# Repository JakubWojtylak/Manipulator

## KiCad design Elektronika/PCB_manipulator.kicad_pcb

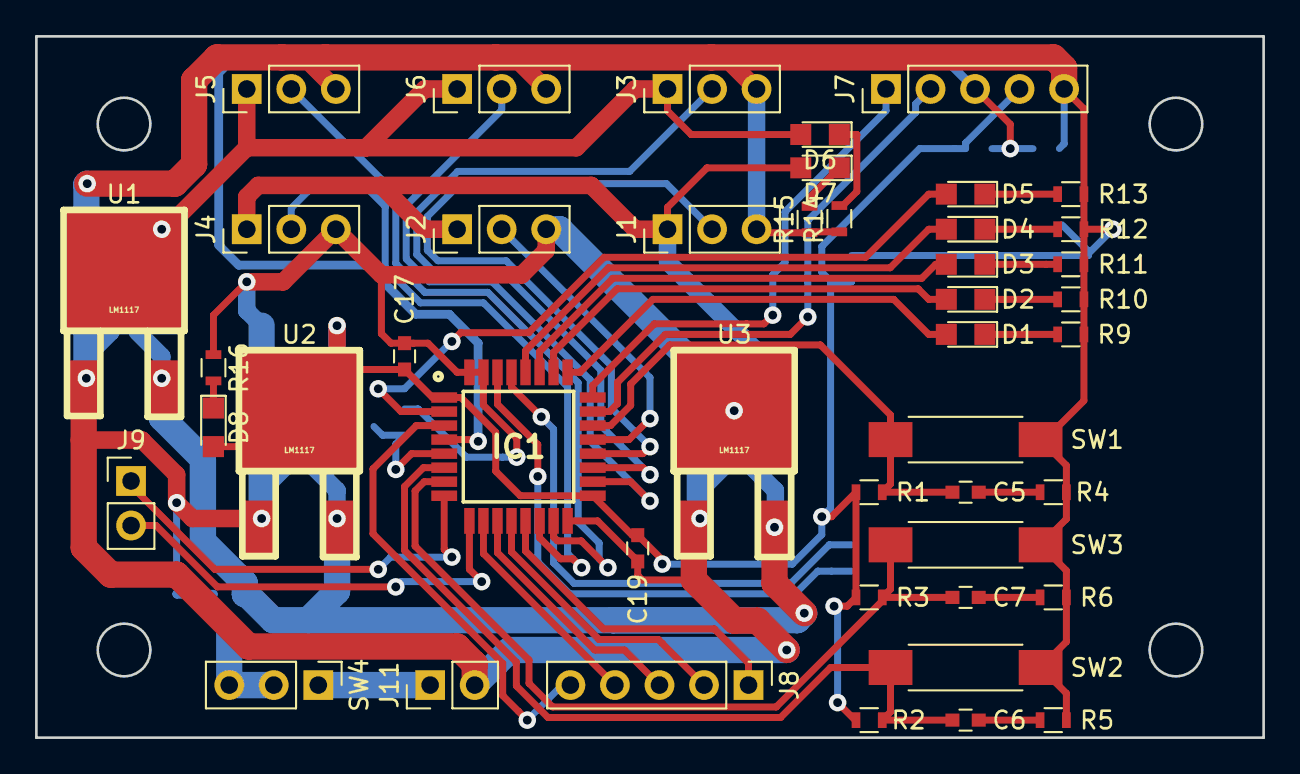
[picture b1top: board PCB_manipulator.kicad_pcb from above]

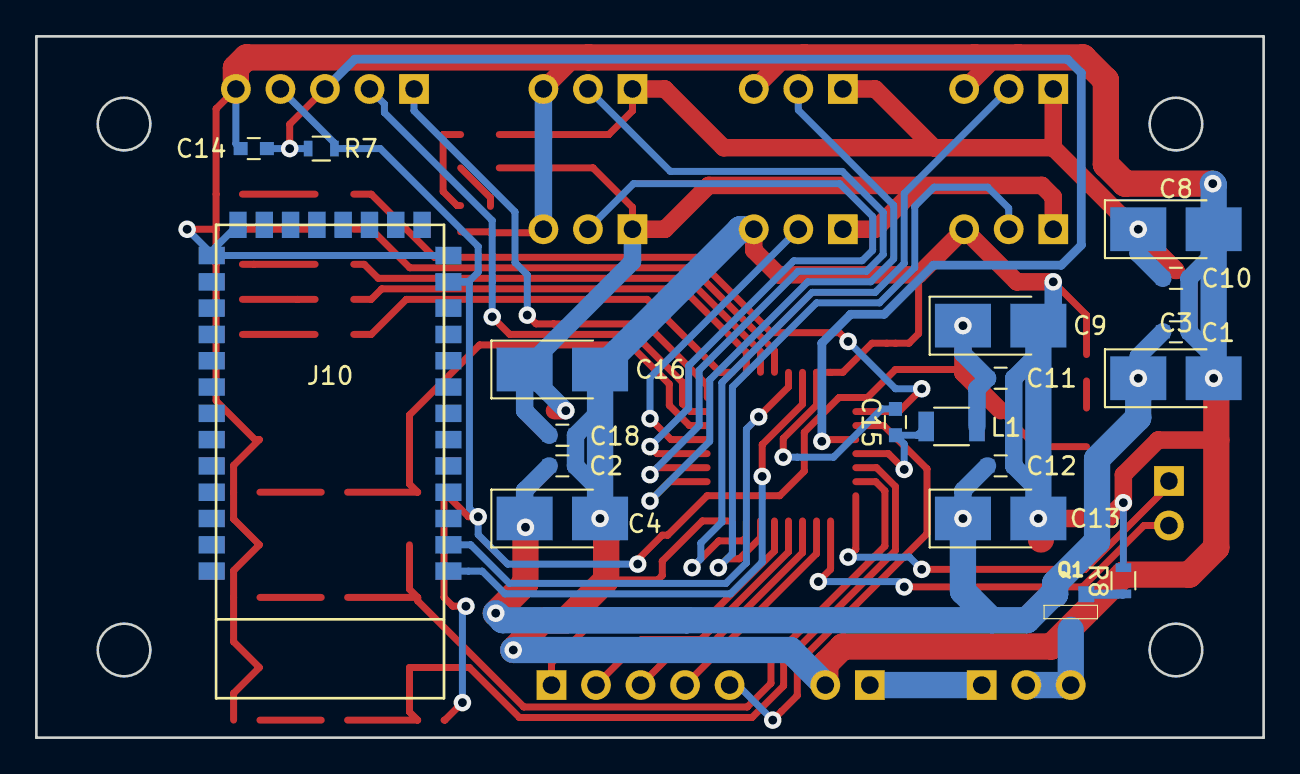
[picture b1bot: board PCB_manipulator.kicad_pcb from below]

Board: 2 copper layers, 70.0 x 40.0 mm, 64 parts (19 on the bottom side), 46 nets.

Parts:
C1, C2, C5, C6, C7, C10, C11, C12, C14, C15, C17, C18, C19: 100nF; C_0603
C3, C4, C8, C9, C13, C16: 10uF; CP_Tantalum_Case-B_EIA-3528-21_Hand
D1, D2, D3, D4, D5, D6, D7, D8: LED; LED_0805
IC1: STM32F051K8T6; QFP80P900X900X160-32N
J1, J2, J3, J4, J5, J6: Conn_01x03; Pin_Header_Straight_1x03_Pitch2.54mm
J7, J8: Conn_01x05; Pin_Header_Straight_1x05_Pitch2.54mm
J9, J11: Conn_01x02; Pin_Header_Straight_1x02_Pitch2.54mm
J10: Conn_01x34; HC-06
L1: L; L_1206
Q1: Q_PMOS_DGS; SOT23EBC
R1, R2, R3: 4,7k; R_0603
R4, R5, R6: 100; R_0603
R7: 100k; R_0603
R8: 1k; R_0603
R9, R10, R11, R12, R13, R14, R15, R16: 330R; R_0603
SW1, SW2, SW3: SW_Push; SW_SPST_REED_CT05-XXXX-G1
SW4: SW_SPDT; Pin_Header_Straight_1x03_Pitch2.54mm
U1, U2, U3: LM1117; LM1117_TO-252

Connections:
5V1: C8.1, C10.1, D6.2, J3.1, J5.1, J6.1, U1.2
5V2: C16.1, C18.1, D7.2, J1.1, J2.1, J4.1, U3.2
+3V3: C9.1, C11.1, C17.1, C19.2, D8.2, IC1.1, IC1.17, J7.4, J10.12, L1.2, R1.1, R2.1, R3.1, R7.2, U2.2
ADC1: IC1.13, J8.1
ADC2: IC1.12, J8.2
ADC3: IC1.11, J8.3
ADC4: IC1.10, J8.4
BT_RX: IC1.30, J10.1
BT_TX: IC1.29, J10.2
BUTTON1: C5.2, IC1.22, R1.2, SW1.1
BUTTON2: C7.2, IC1.7, R3.2, SW3.1
BUTTON3: C6.2, IC1.6, R2.2, SW2.1
GND: C1.2, C2.2, C3.2, C4.2, C8.2, C9.2, C10.2, C11.2, C12.2, C13.2, C14.2, C15.2, C16.2, C17.2, C18.2, C19.1, IC1.16, IC1.31, IC1.32, J1.3, J2.3, J3.3, J4.3, J5.3, J6.3, J7.5, J10.13, J10.21, J10.22, J11.2, R4.1, R5.1, R6.1, R8.2, R9.1, R10.1, R11.1, R12.1, R13.1, R14.1, R15.1, R16.1, SW1.2, SW2.2, SW3.2, U1.3, U2.3, U3.3
LED1: D1.2, IC1.25
LED2: D2.2, IC1.26
LED3: D3.2, IC1.27
LED4: D4.2, IC1.28
LED5: D5.2, IC1.2
unnamed: C5.1, R4.2
unnamed: C6.1, R5.2
unnamed: C7.1, R6.2
unnamed: C15.1, IC1.5, L1.1
unnamed: D1.1, R9.2
unnamed: D2.1, R10.2
unnamed: D3.1, R11.2
unnamed: D4.1, R12.2
unnamed: D5.1, R13.2
unnamed: D6.1, R14.2
unnamed: D7.1, R15.2
unnamed: D8.1, R16.2
unnamed: Q1.3, SW4.2, SW4.3
unnamed: Q1.2, R8.1
OUT1: IC1.3, J8.5
PWM1: IC1.21, J2.2
PWM2: IC1.20, J1.2
PWM3: IC1.19, J3.2
PWM4: IC1.18, J6.2
PWM5: IC1.15, J5.2
PWM6: IC1.14, J4.2
RESET: C14.1, IC1.4, J7.3, R7.1
SWCLK: IC1.24, J7.1
SWDIO: IC1.23, J7.2
USART_RX: IC1.9, J9.2
USART_TX: IC1.8, J9.1
VCC: J11.1, SW4.1
VIN: C1.1, C2.1, C3.1, C4.1, C12.1, C13.1, Q1.1, U1.1, U2.1, U3.1

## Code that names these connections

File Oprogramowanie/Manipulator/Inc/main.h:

/* USER CODE BEGIN Header */
/**
  ******************************************************************************
  * @file           : main.h
  * @brief          : Header for main.c file.
  *                   This file contains the common defines of the application.
  ******************************************************************************
  * @attention
  *
  * <h2><center>&copy; Copyright (c) 2019 STMicroelectronics.
  * All rights reserved.</center></h2>
  *
  * This software component is licensed by ST under BSD 3-Clause license,
  * the "License"; You may not use this file except in compliance with the
  * License. You may obtain a copy of the License at:
  *                        opensource.org/licenses/BSD-3-Clause
  *
  ******************************************************************************
  */
/* USER CODE END Header */

/* Define to prevent recursive inclusion -------------------------------------*/
#ifndef __MAIN_H
#define __MAIN_H

#ifdef __cplusplus
extern "C" {
#endif

/* Includes ------------------------------------------------------------------*/
#include "stm32f0xx_hal.h"

/* Private includes ----------------------------------------------------------*/
/* USER CODE BEGIN Includes */

/* USER CODE END Includes */

/* Exported types ------------------------------------------------------------*/
/* USER CODE BEGIN ET */

/* USER CODE END ET */

/* Exported constants --------------------------------------------------------*/
/* USER CODE BEGIN EC */

/* USER CODE END EC */

/* Exported macro ------------------------------------------------------------*/
/* USER CODE BEGIN EM */

/* USER CODE END EM */

/* Exported functions prototypes ---------------------------------------------*/
void Error_Handler(void);

/* USER CODE BEGIN EFP */
/* USER CODE END EFP */

/* Private defines -----------------------------------------------------------*/
#define LED5_Pin GPIO_PIN_0
#define LED5_GPIO_Port GPIOF
#define Button1_Pin GPIO_PIN_0
#define Button1_GPIO_Port GPIOA
#define Button2_Pin GPIO_PIN_1
#define Button2_GPIO_Port GPIOA
#define LED1_Pin GPIO_PIN_15
#define LED1_GPIO_Port GPIOA
#define LED2_Pin GPIO_PIN_3
#define LED2_GPIO_Port GPIOB
#define LED3_Pin GPIO_PIN_4
#define LED3_GPIO_Port GPIOB
#define LED4_Pin GPIO_PIN_5
#define LED4_GPIO_Port GPIOB
/* USER CODE BEGIN Private defines */

/* USER CODE END Private defines */

#ifdef __cplusplus
}
#endif

#endif /* __MAIN_H */

/************************ (C) COPYRIGHT STMicroelectronics *****END OF FILE****/

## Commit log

2020-03-28 Manipulator_finished
    University project for manipulator from scratch
